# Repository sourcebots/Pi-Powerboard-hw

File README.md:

# Pi-Powerboard-hw
Design for powering raspberry pi through GPIO

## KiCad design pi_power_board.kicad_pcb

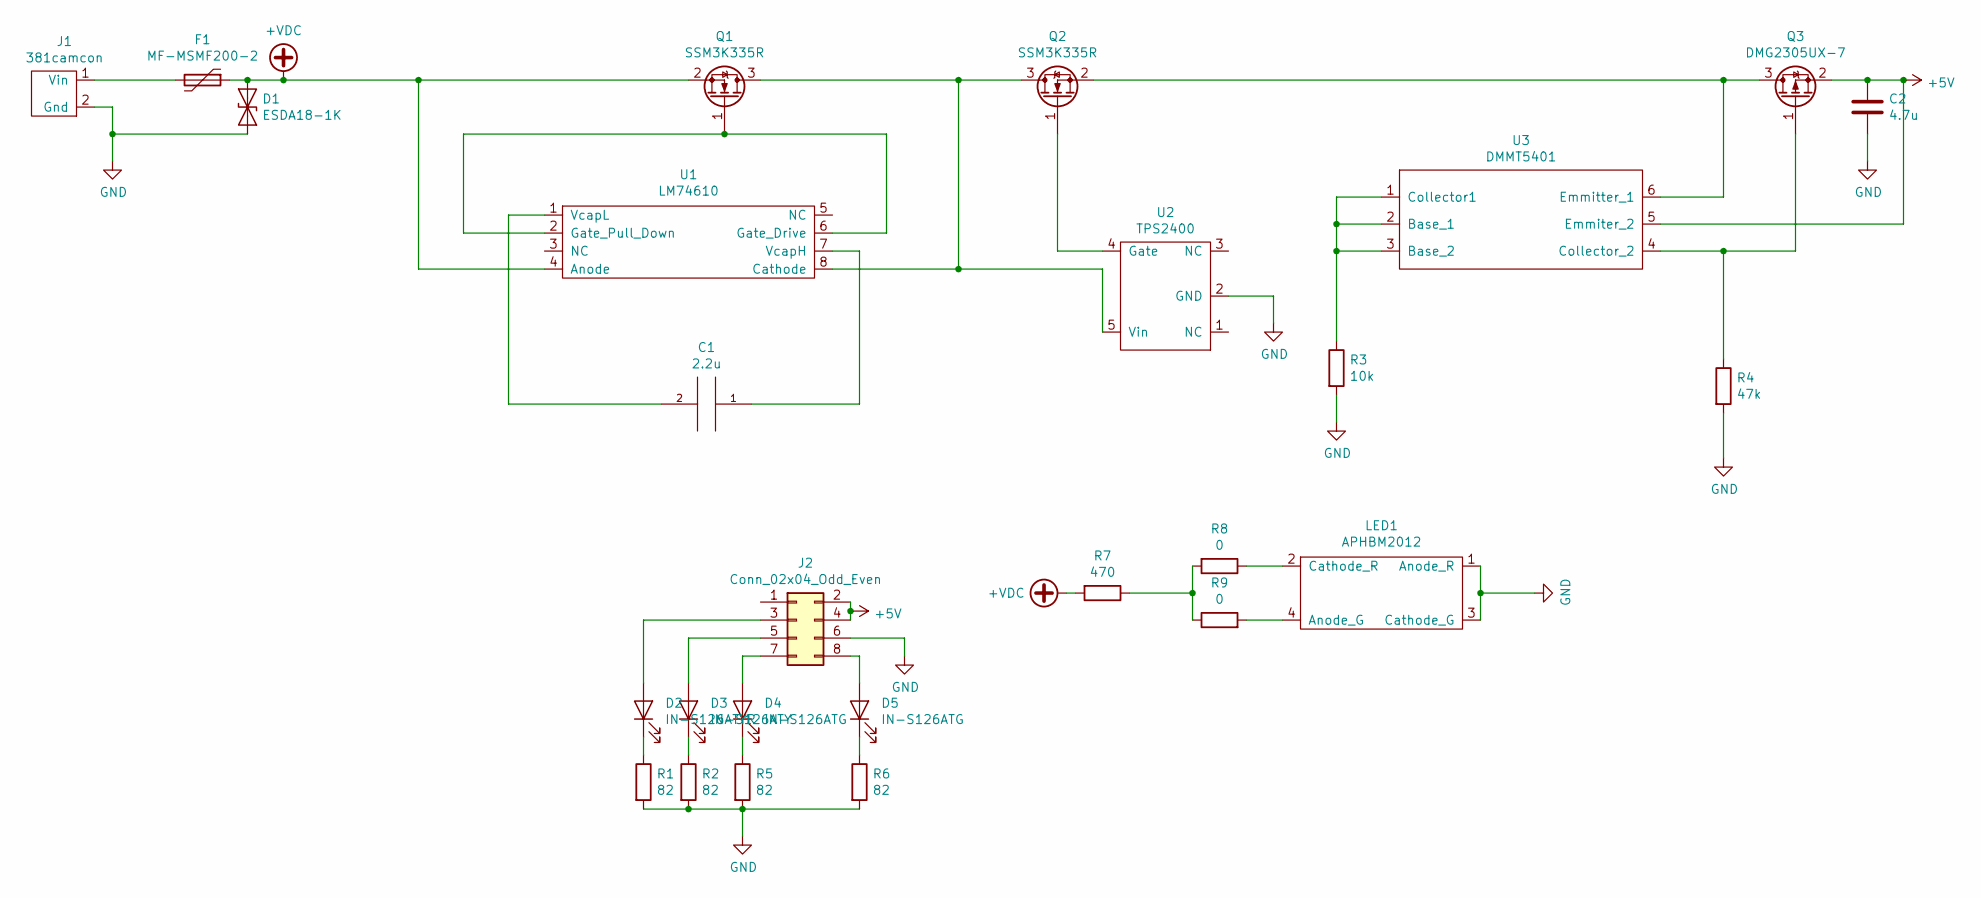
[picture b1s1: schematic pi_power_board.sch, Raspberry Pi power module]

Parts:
C1: 2.2u; C_0805_2012Metric_Pad1.15x1.40mm_HandSolder
C2: 4.7u; C_1206_3216Metric_Pad1.42x1.75mm_HandSolder
D1: ESDA18-1K; D_SOD-523
D2: IN-S126ATYR; LED_1206_3216Metric_Pad1.42x1.75mm_HandSolder
D3: IN-S126ATY; LED_1206_3216Metric_Pad1.42x1.75mm_HandSolder
D4, D5: IN-S126ATG; LED_1206_3216Metric_Pad1.42x1.75mm_HandSolder
F1: MF-MSMF200-2; Fuse_1812_4532Metric_Pad1.30x3.40mm_HandSolder
J1: 381camcon
J2: Conn_02x04_Odd_Even; BG120-08-A-0-N-D
LED1: APHBM2012
Q1, Q2: SSM3K335R; SOT-23
Q3: DMG2305UX-7; SOT-23
R1, R2, R5, R6: 82; R_0805_2012Metric_Pad1.15x1.40mm_HandSolder
R3: 10k; R_0805_2012Metric_Pad1.15x1.40mm_HandSolder
R4: 47k; R_0805_2012Metric_Pad1.15x1.40mm_HandSolder
R7: 470; R_0805_2012Metric_Pad1.15x1.40mm_HandSolder
R8, R9: 0; R_0805_2012Metric_Pad1.15x1.40mm_HandSolder
U1: LM74610
U2: TPS2400; SOT-23-5
U3: DMMT5401

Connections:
+5V: C2.2, J2.2, J2.4, Q3.2 (S), U3.5 (Emmiter_2)
+VDC: D1.1 (A1), F1.1, Q1.2 (S), R7.2, U1.4 (Anode)
GND: C2.1, D1.2 (A2), J1.2 (Gnd), J2.6, LED1.1 (Anode_R), LED1.3 (Cathode_G), R1.2, R2.2, R3.2, R4.2, R5.2, R6.2, U2.2 (GND)
unnamed: C1.1, U1.7 (VcapH)
unnamed: C1.2, U1.1 (VcapL)
unnamed: D2.1 (K), R1.1
unnamed: D2.2 (A), J2.3
unnamed: D3.1 (K), R2.1
unnamed: D3.2 (A), J2.5
unnamed: D4.1 (K), R5.1
unnamed: D4.2 (A), J2.7
unnamed: D5.1 (K), R6.1
unnamed: D5.2 (A), J2.8
unnamed: F1.2, J1.1 (Vin)
unnamed: LED1.2 (Cathode_R), R8.1
unnamed: LED1.4 (Anode_G), R9.2
unnamed: Q1.1 (G), U1.2 (Gate_Pull_Down), U1.6 (Gate_Drive)
unnamed: Q1.3 (D), Q2.3 (D), U1.8 (Cathode), U2.5 (Vin)
unnamed: Q2.1 (G), U2.4 (Gate)
unnamed: Q2.2 (S), Q3.3 (D), U3.6 (Emmitter_1)
unnamed: Q3.1 (G), R4.1, U3.4 (Collector_2)
unnamed: R3.1, U3.1 (Collector1), U3.2 (Base_1), U3.3 (Base_2)
unnamed: R7.1, R8.2, R9.1

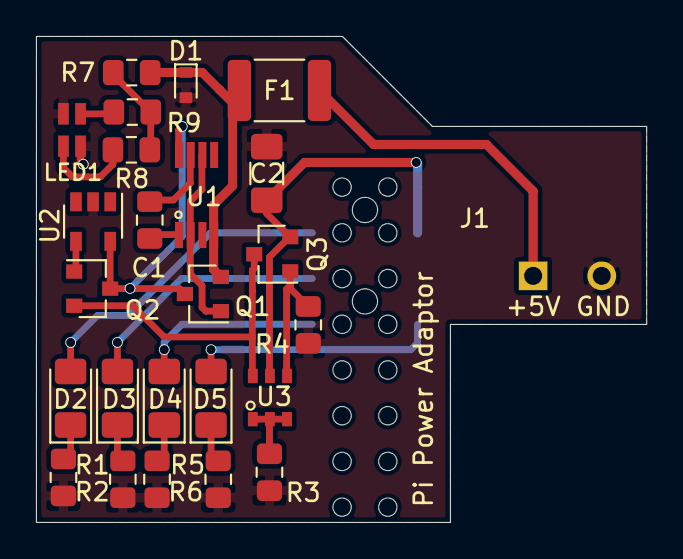
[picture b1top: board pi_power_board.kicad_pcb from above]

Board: 2 copper layers, 33.9 x 27.0 mm, 26 parts (0 on the bottom side), 23 nets.

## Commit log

2019-06-10 Upload of design and libraries
2019-06-11 fixed issue with board edges
2019-06-26 Change header to SMT W/through holes
2019-07-14 Removed ignored files
2019-07-15 Added Details to schematic border
2019-07-15 Manufacturability changes and dimension fixing
2019-07-15 Added page frame data
2019-07-15 Updated Master component footprint
2019-07-15 DRC fixes
2019-07-15 Updated camcon hole size
2019-11-23 Added schematic to README as svg
2021-11-29 Create LICENSE
    Added CC0 license
